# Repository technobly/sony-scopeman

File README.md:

# Sony-Scopeman

Hardware Design files of a replacement mainboard for the Sony Watchman FD-10A. This turns it into a bluetooth and Wi-Fi-enabled vector display.

# Features
There are two modes which can be selected via the power switch:

* In "Audio" mode, the ESP32 acts as a bluetooth speaker. Play back audio files from your smartphone or laptop to hear and see the soundwaves. You can change the size by adjusting the playback volume

    [Audio Demo](https://twitter.com/FauthNiklas/status/1337467949318279170)

* In "Video" mode, the ESP32 renders the result of the Lorenz Attractor equation. You can change the simulation speed using the "Tune" knob.

    [Video Demo](https://twitter.com/FauthNiklas/status/1339650704584171522)

# Instructions

You'll need:

* Sony Watchman Model FD-10A
* Pre-assembled replacemend mainboard (eg. from JLCPCB assembly)
* Two 803040 (1000mAh) Lipo batteries with JST-PH 2.0mm connector

Open the Sony Watchman and unscrew the original mainboard. Make sure to keep all the screws in a safe place.

Unsolder all wires from the mainboard.

Unsolder (and unscrew) these components from the mainboard. We'll need them for our replacement.

Your trimmer pots might also be a different style, but check that they are the same 5k ohm value ("502").

Install all unsoldered components on the replacement mainboard.

Unsolder the speaker cables (black and white) from the flyback PCB. Solder them to the replacement PCB (take care of polarity. White is closer to the ESP32).
Remove all other cables from the flyback PCB except for blue, yellow, black and purple.

Your speaker wires might not be black and white, but both black.  There is a polarity of the speaker, and the positive (+) was marked with red paint/glyptol.  You might also have to extend your speaker wires.

Solder the blue (flyback signal) and yellow (blanking) to the new mainboard.
Do the same for purple (supply) and black (GND).

Next, connect the deflection coil wires (purple, white, red and blue). 

Here are more pictures of the assembled unit.
:mag: CLICK FOR A LARGER IMAGE!

:pencil2: If you want to slowly bring up your board and not let the magic smoke out, here are some things you can do:

- Use a current limited power supply and make a cable that plugs into the JST2.0 connector.  Set your power supply to 4V at 500mA.
- When the device normally powers on it draws about 300mA.  If it draws 500mA you probably have a short circuit somewhere.
- Check the +3.3V output (it should be about +3.3V)
- Check the -3.3V output (it should be about -3.7V)
- :warning: Check the FLYBACK output, it should be toggling at 16kHz @ 40% duty cycle.  If it's continuously LOW, it will make the power supply draw infinite amounts of current.  It should be pulled up to +3.3V when the ESP32 is reset/programming via R50.

You'll proabably want to play with it for a while and make sure everything is working well before moving on to the final steps.

You can now plug in the batteries (make sure the watchman is turned off) and screw the mainboard back in place. You need two screws for this (mind the arrows on the back of the PCB).

Now you can add a slothole to the lower half of the case for the USB type C jack. You also need to brake away some plastics to make space for the new batteries. No worries, if done correctly this won't be visible from the outside and the battery cover will still close.

Something really handy for these mods is the [Dremel 1/16" ballnose cutter (#109)](https://www.amazon.com/Dremel-109-Engraving-Cutter-16-inch/dp/B0006N72X4).  I got mine in an [11 piece Carving/Engraving Kit](https://www.amazon.com/Dremel-729-01-Engraving-Accessories-11-Piece/dp/B09FP387V2).  This is also really good for the USB-C cut-out.

That's it! Before you screw the watchman back together and store the batteries behind the cover, you may want to adjust the two potentiometers on the mainboard to center the image. But first you need to flash the firmware. Turn on the watchman and connect it via USB. You can then flash the ESP32 using the Arduino IDE (make sure to select "Board: ESP Wrover Module").

You might also need to readjust the focus. This can be done from outside using the original focus knob (hidden behind a small hole at the side).

# Credits

Deflection coil drivers inspired by http://www.e-basteln.de/file/asteroids/Vectrex_XY_Driver.pdf

A2DP Arduino lib for ESP32: https://github.com/pschatzmann/ESP32-A2DP

# Ordering

See the [BOM README.md](hardware/bom-vectorboy-v1.3/README.md)

:warning: **NOTE: Be sure to order the PCB thinner than standard, 0.040" (1.0mm) should be good.**  If you end up ordering as 0.062" (1.6mm), [you will have to make a bunch of modifications, but it can be done.](hardware/bom-vectorboy-v1.3/thick-pcb-mods.md)

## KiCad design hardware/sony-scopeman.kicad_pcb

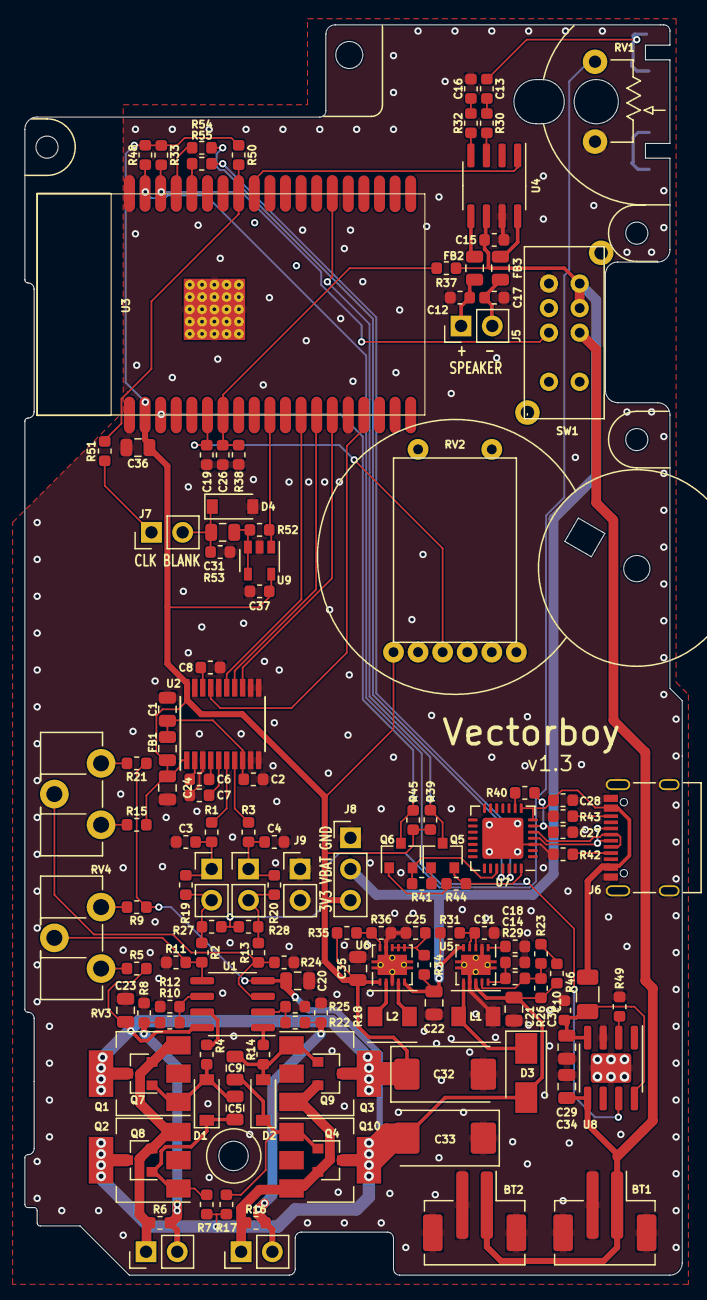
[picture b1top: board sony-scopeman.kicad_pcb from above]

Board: 2 copper layers, 53.5 x 101.8 mm, 135 parts (0 on the bottom side), 87 nets.

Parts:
BT1, BT2: LiIon; JST_PH_B2B-PH-SM4-TB_1x02-1MP_P2.00mm_Vertical
C1, C5, C9, C20, C21, C22, C23, C24, C29, C31, C34, C35, C36: 10u; C_0805_2012Metric
C2, C8, C11, C14, C19, C25, C26, C27, C28, C30, C37: 100n; C_0603_1608Metric
C3, C4: 2.2n; C_0603_1608Metric
C6, C7: 2.2u; C_0603_1608Metric
C10: 10pF; C_0603_1608Metric
C12, C17: 220p; C_0603_1608Metric
C13, C16: 1u; C_0603_1608Metric
C15: 10u; C_0603_1608Metric
C18: 4.7n; C_0603_1608Metric
C32, C33: 100u; CP_EIA-7343-43_Kemet-X
D1, D2, D4: 4148; D_SOD-123
D3: SS34; D_SMA
FB1, FB2, FB3: 601; L_0805_2012Metric
J1: EXT_X; PinHeader_1x02_P2.54mm_Vertical
J2: COIL_X; PinHeader_1x02_P2.54mm_Vertical
J3: EXT_Y; PinHeader_1x02_P2.54mm_Vertical
J4: COIL_Y; PinHeader_1x02_P2.54mm_Vertical
J5: SPEAKER; PinHeader_1x02_P2.54mm_Vertical
J6: USB_C_Receptacle_USB2.0; USB_C_Receptacle_Palconn_UTC16-G
J7: BLK+CLK; PinHeader_1x02_P2.54mm_Vertical
J8: PWR; PinHeader_1x03_P2.54mm_Vertical
J9: GND; PinHeader_1x02_P2.54mm_Vertical
L1: 4.7u; Inductor_4040
L2: 2.2u; Inductor_4040
Q1, Q3: PZT3904; SOT-223-3_TabPin2
Q2, Q4: PZT3906; SOT-223-3_TabPin2
Q5, Q6: MMBT3904; SOT-23
Q7, Q9: STN851; SOT-23
Q8, Q10: STN951; SOT-23
R1, R3, R10, R11, R22: 470; R_0603_1608Metric
R2, R7, R13, R17, R54, R55: 1k; R_0603_1608Metric
R4, R14, R31: 10; R_0603_1608Metric
R5, R9, R15, R21, R39, R40, R41, R44, R45, R50: 10k; R_0603_1608Metric
R6, R16: 3.3k; R_0603_1608Metric
R8, R18: 4.7R; R_0603_1608Metric
R12, R24, R25, R36, R52: DNP; R_0603_1608Metric
R19, R20, R35: 0R; R_0603_1608Metric
R23, R33, R37, R38, R48: 100k; R_0603_1608Metric
R26: 220k; R_0603_1608Metric
R27, R28: 22k; R_0603_1608Metric
R29: 75k; R_0603_1608Metric
R30, R32, R34: 100; R_0603_1608Metric
R42, R43: 5.1k; R_0603_1608Metric
R46: 0.27R; R_1206_3216Metric
R49: 1.2k; R_0603_1608Metric
R51: 22; R_0603_1608Metric
R53: TBD; R_0603_1608Metric
RV1: 10k; sony_volume
RV2: 180k; sony_tune
RV3, RV4: 10k; Potentiometer_ACP_CA9-H3,8_Horizontal
SW1: Power Switch; sony_slide_switch
U1: OPA2683; SOIC-8_3.9x4.9mm_P1.27mm
U2: PCM5102; TSSOP-20_4.4x6.5mm_P0.65mm
U3: ESP32-WROVER
U4: PAM8302AAD; SOIC-8_3.9x4.9mm_P1.27mm
U5: TPS63700DRCT; Texas_DRC0010J_ThermalVias
U6: TPS63001; Texas_DRC0010J_ThermalVias
U7: CP2102N-A01-GQFN28; QFN-28-1EP_5x5mm_P0.5mm_EP3.35x3.35mm
U8: TP4056-otter; SOIC-8-1EP_3.9x4.9mm_P1.27mm_EP2.41x3.3mm
U9: LMV321; SOT-23-5

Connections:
+3V3: C23.1, C24.1, C32.1, C35.1, C36.1, C37.1, FB1.1, J8.3, Q1.2, Q3.2, Q7.3, Q9.3, R5.2, R15.2, R33.1, R35.1, R39.2, R45.2, R48.1, R50.1, RV2.1, U1.8, U2.1, U2.20, U3.2, U6.1, U9.5
+4V: C15.1, C22.1, J8.2, R31.2, R34.1, R37.1, SW1.1, SW1.3, U4.6, U5.5, U6.5
+5V: C28.1, J6.A4, J6.A9, J6.B4, J6.B9, R46.1, U7.7, U7.8
-3V3: C10.2, C20.1, C21.1, C33.2, D3.2, Q2.2, Q4.2, Q8.3, Q10.3, R7.1, R9.1, R17.1, R21.1, R26.2, U1.4, U5.8
CHRG_STAT: R48.2, U3.37, U8.7
DAC_BCK: U2.13, U3.14
DAC_DATA: U2.14, U3.13
DAC_LRCK: U2.15, U3.12
ESP32_DAC0: R52.2, U3.10, U9.1
ESP32_FLASH: Q5.3, R39.1, U3.25
ESP32_PWM: R50.2, R51.1, U3.31
ESP32_RESET: Q6.3, R45.1, U3.3
ESP32_RXD: R55.1, U7.26
ESP32_TXD: R54.1, U7.25
GND: BT1.2, BT2.2, C1.2, C2.2, C3.1, C4.2, C7.2, C8.2, C11.2, C12.2, C14.2, C15.2, C16.2, C17.2, C18.2, C19.2, C20.2, C21.2, C22.2, C23.2, C24.2, C25.2, C26.2, C27.2, C28.2, C29.2, C30.2, C32.2, C33.1, C34.2, C35.2, C36.2, C37.2, D4.2, J6.A1, J6.A12, J6.B1, J6.B12, J6.S1, J8.1, J9.1, J9.2, L1.1, R8.2, R11.1, R12.2, R18.2, R24.1, R25.2, R36.2, R38.2, R42.1, R43.1, R49.2, R53.2, RV1.1, RV2.3, SW1.6, U2.3, U2.9, U2.10, U2.11, U2.12, U2.16, U2.19, U3.1, U3.15, U3.38, U3.39, U4.7, U5.2, U5.7, U5.11, U6.3, U6.9, U6.11, U7.3, U7.29, U8.3, U8.9, U9.2
unnamed: C1.1, C2.1, FB1.2, U2.8
unnamed: C3.2, J1.1, R1.1, R19.2
unnamed: C4.1, J3.1, R3.1, R20.2
unnamed: C5.1, D1.2, Q1.1, Q7.1, R4.1
unnamed: C5.2, D1.1, Q2.1, Q8.1, R7.2
unnamed: C6.1, U2.2
unnamed: C6.2, U2.4
unnamed: C7.1, U2.5
unnamed: C8.1, U2.18
unnamed: C9.1, D2.2, Q3.1, Q9.1, R14.1
unnamed: C9.2, D2.1, Q4.1, Q10.1, R17.2
unnamed: C10.1, R23.2
unnamed: C11.1, R31.1, U5.3, U5.4
unnamed: C12.1, FB2.1, J5.1
unnamed: C13.1, R30.2
unnamed: C13.2, RV1.2
unnamed: C14.1, R29.1, U5.10
unnamed: C16.1, R32.2
unnamed: C17.1, FB3.2, J5.2
unnamed: C18.1, U5.1
unnamed: C25.1, R34.2, U6.6, U6.7, U6.8
unnamed: C29.1, C30.1, R46.2, U8.4, U8.8
unnamed: C31.1, D4.1, J7.2, R53.1
unnamed: C31.2, R52.1, U9.3, U9.4
unnamed: D3.1, L1.2, U5.6
unnamed: FB2.2, U4.5
unnamed: FB3.1, U4.8
unnamed: J1.2, R2.2, R19.1, R27.2
unnamed: J2.1, Q1.3, Q2.3, Q7.2, Q8.2, R6.1
unnamed: J2.2, R6.2, R8.1, R10.1
unnamed: J3.2, R13.2, R20.1, R28.2
unnamed: J4.1, Q3.3, Q4.3, Q9.2, Q10.2, R16.1
unnamed: J4.2, R16.2, R18.1, R22.1
unnamed: J6.A5, R42.2
unnamed: J6.A6, J6.B6, U7.4
unnamed: J6.A7, J6.B7, U7.5
unnamed: J6.B5, R43.2
unnamed: J7.1, R51.2
unnamed: L2.1, U6.4
unnamed: L2.2, U6.2
unnamed: Q5.1, R41.1
unnamed: Q5.2, R44.2, U7.28
unnamed: Q6.1, R44.1
unnamed: Q6.2, R41.2, U7.24
unnamed: R1.2, U2.6
unnamed: R3.2, U2.7
unnamed: R4.2, U1.7
unnamed: R5.1, RV3.1
unnamed: R9.2, RV3.3
unnamed: R10.2, R12.1, U1.6
unnamed: R2.1, R11.2, RV3.2, U1.5
unnamed: R13.1, R24.2, RV4.2, U1.3
unnamed: R14.2, U1.1
unnamed: R15.1, RV4.1
unnamed: R21.2, RV4.3
unnamed: R22.2, R25.1, U1.2
unnamed: R23.1, R26.1, R29.2, U5.9
unnamed: R27.1, R28.1, RV1.3
unnamed: R30.1, U4.3
unnamed: R32.1, U4.4
unnamed: R35.2, R36.1, U6.10
unnamed: R40.1, U7.9
unnamed: R49.1, U8.2
unnamed: R54.2, U3.35
unnamed: R55.2, U3.34
PA_UNMUTE: U3.30, U4.1
PCM_UNMUTE: U2.17, U3.16
PWR_SW: R33.2, SW1.5, U3.36
TUNE_POT: C19.1, RV2.2, U3.6
VBAT_SNS: C26.1, R37.2, R38.1, U3.7
VBUS: BT1.1, BT2.1, C34.1, SW1.2, U8.5
VDD: C27.1, R40.2, U7.6

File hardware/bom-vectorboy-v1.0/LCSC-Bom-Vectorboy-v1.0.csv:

LCSC Part Number,Customer Part Number,Footprint,Value,Quantity,,,
C1017,"FB3,FB2,FB1",L_0805_2012Metric,601,3,,,
C1603,"C17,C12",0603_C,220p,2,,,
C1604,"C4,C3",0603_C,2.2n,2,,,
C1634,C10,0603_C,10pF,1,,,
C1691,C15,0603_C,10u,1,,,
C6568,U7,QFN-28-1EP_5x5mm_P0.5mm_EP3.35x3.35mm,CP2102N-A01-GQFN28,1,,,
C8678,D3,D_SMA,SL03,1,,,
C14663,"C37,30,28-25,19,14,11,8,2",0603_C,100n,11,,,
C15849,"C16,C13",0603_C,1u,2,,,
C95841,"C36,35,34,31,29,24-20,9,5,1",0805_C,10u,13,,,
C16581,U8,SOIC-8-1EP_3.9x4.9mm_P1.27mm_EP2.41x3.3mm,TP4056-otter,1,,,
C21189,"R35,R20,R19",0603_R,0R,3,,,
C21190,"R55-53,R17,R13,R7,R2",0603_R,1k,7,,,
C22765,R49,0603_R,1.2k,1,,,
C22775,"R34,R32,R30",0603_R,100,3,,,
C22859,"R31,R14,R4",0603_R,10,3,,,
C2849052,"R18,R8",0603_R,4.7R,2,,,
C22961,R26,0603_R,220k,1,,,
C22978,"R16,R6",0603_R,3.3k,2,,,
C23179,"R22,R11,R10,R3,R1",0603_R,470,6,,,
C23186,"R43,R42",0603_R,5.1k,2,,,
C23345,R51,0603_R,22,1,,,
C23630,"C7,C6",0603_C,2.2u,2,,,
C308471,R46,R_1206_3216Metric,0.27R,1,,,
C25803,"R48,R38,R37,R33,R23",0603_R,100k,5,,,
C25804,"R50,45,44,41-39",0603_R,10k,7,,,
C18671,R29,0603_R,75k,1,,,
C28060,U6,Texas_DRC0010J_ThermalVias,TPS63001,1,,,
C31850,"R28,R27,R21,R15,R9,R5",0603_R,22k,6,,,
C53987,C18,0603_C,4.7n,1,,,
C54792,U5,Texas_DRC0010J_ThermalVias,TPS63700DRCT,1,,,
C81598,"D4,D2,D1",D_SOD-123,4148,3,,,
C107671,U2,TSSOP-20_4.4x6.5mm_P0.65mm,PCM5102,1,,,
C111113,"Q5,Q6",SOT-23,MMBT3904,2,,,
C112137,U4,SOIC-8_150mil,PAM8302AAD,1,,,
C133359,"Q1,Q3",SOT-223,STN851,2,,,
C133360,"Q2,Q4",SOT-223,STN951,2,,,
C155463,"C33,C32",CP_EIA-7343-43_Kemet-X,100u,2,,,
C265003,"BT1,BT2",JST_PH_B2B-PH-SM4-TB_1x02-1MP_P2.00mm_Vertical,LiIon,2,,,
C165948,J6,USB_C_Receptacle_Palconn_UTC16-G,TYPE-C-31-M-12,1,,,
C520302,L2,Inductor_4040,2.2u,1,,,
C520304,L1,Inductor_4040,4.7u,1,,,
C686637,U9,SOT-23-5,LMV321,1,,,

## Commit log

2022-02-19 adds LCSC compatible BOM and README.md for how to order
2022-03-21 update boms with errors found during build.
    Everything should work now if building from the bags of parts you receive
2022-03-22 more updates to README.md and BOM
2022-03-22 fix/update software PWM/warnings, add more examples
2022-08-28 add software keystone correction
2022-08-28 more docs updates
2022-08-29 fixes up some confusing dual footprints - v1.3
2022-08-29 Make all Vectorboy files v1.3 to keep things aligned
2022-08-29 [v1.3] fix Q1-Q4 3D render and move BT1/BT2 onto the board
2022-08-31 fix BOM for importing and building at JLCPCB
